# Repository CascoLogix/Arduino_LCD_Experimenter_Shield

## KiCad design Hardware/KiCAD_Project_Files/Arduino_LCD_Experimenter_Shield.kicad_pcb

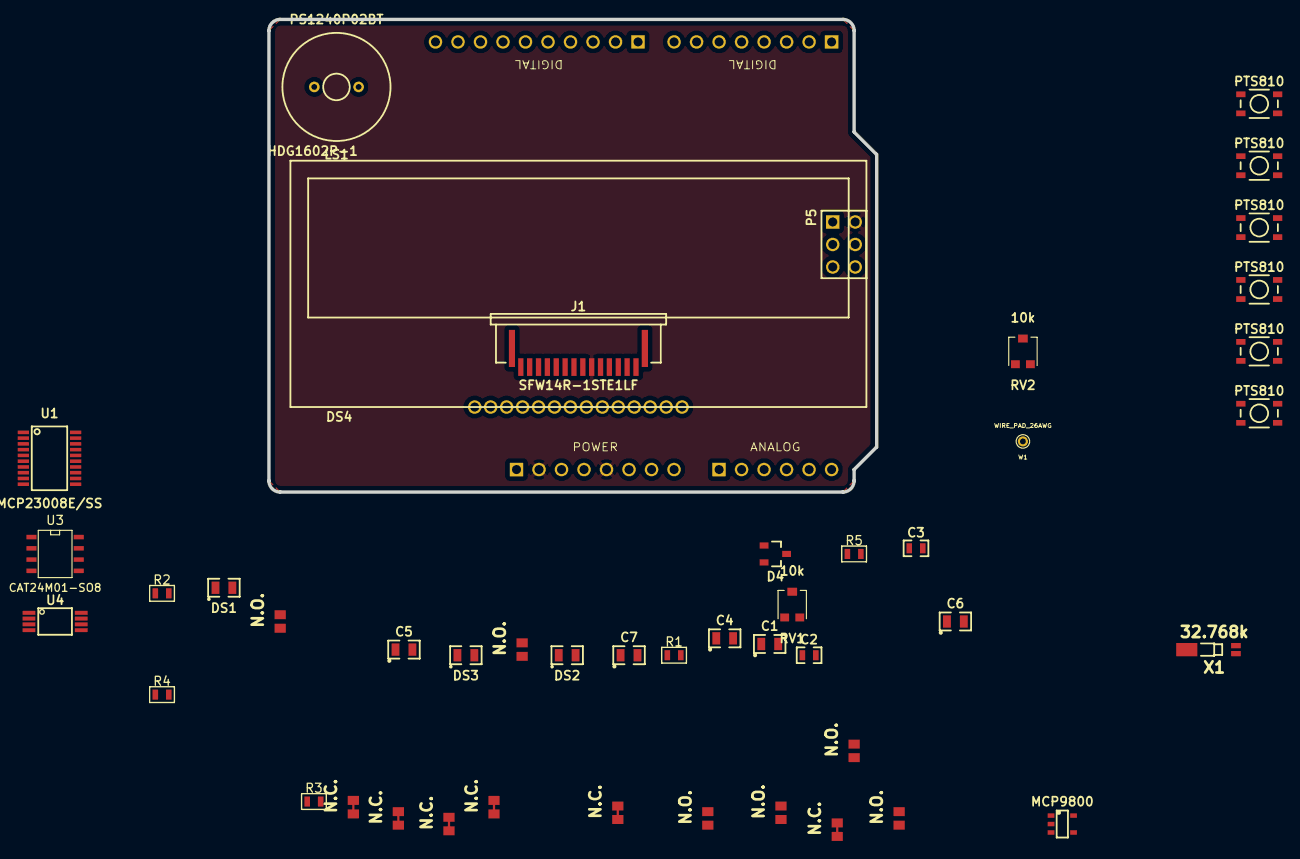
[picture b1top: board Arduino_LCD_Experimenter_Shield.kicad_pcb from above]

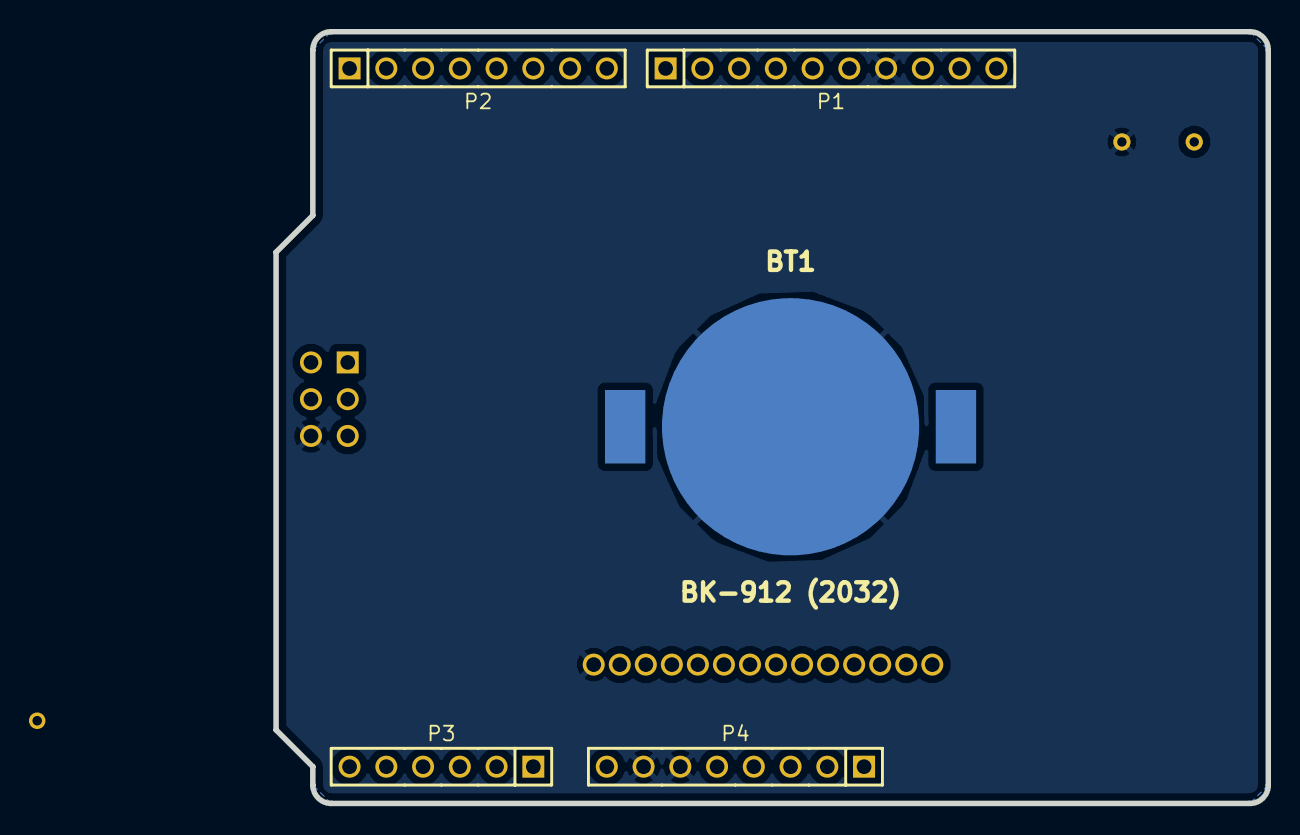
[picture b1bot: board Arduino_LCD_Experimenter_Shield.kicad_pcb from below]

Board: 2 copper layers, 68.6 x 53.3 mm, 51 parts (5 on the bottom side), 46 nets, no tracks yet.

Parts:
BT1: BK-912 (2032); CR2032_MPD_BK912_SMT
C1, C4, C5, C6, C7: 10uF; CP0805
C2, C3: 8pF; C0603
D4: BAV70L; SOT-23-3
DS1, DS2, DS3: YEL; DS0805
DS4: HDG1602P-1
J1: SFW14R-1STE1LF; FFC_14P_1.0MM_SMT
LK1, LK2, LK3, LK7, LK9, LK10: N.O.; SOLDER_LINK_NO
LK4, LK5, LK6, LK8, LK11, LK12: N.C.; SOLDER_LINK_NC
LS1: PS1240P02BT; PS1240P02BT_PTH
P1: 1X10 HEADER; HEADER_M_2.54MM_1R10P_ST_AU_PTH
P2, P4: 1X8 HEADER; HEADER_M_2.54MM_1R8P_ST_AU_PTH
P3: 1X6 HEADER; HEADER_M_2.54MM_1R6P_ST_AU_PTH
P5: 2X3 HEADER; HEADER_100MIL_2R6P_PTH
R1, R2, R3: 270; R0603
R4, R5: 4.7k; R0603
RV1, RV2: 10k; POT_TRIM_PVZ3_SMT
SW1, SW2, SW3, SW4, SW5, SW6: PTS810; PTS810_SMT
U1: MCP23008E/SS; TSSOP-20
U2: MCP9800; SOT-23-5
U3: CAT24M01-SO8; SO-8
U4: MCP7940M-I/ST; TSSOP-8
W1: WIRE_PAD_26AWG
X1: 32.768k; AB26TRQ

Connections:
+5V: C1.1, C4.1, C5.1, C6.1, D4.2, DS4.9, J1.9, LK1.1, LK2.1, LK3.1, LK9.1, LK10.1, P4.2, P4.5, P5.2, R1.1, R2.1, R3.1, R4.1, R5.1, RV1.3, U1.20, U2.1, U3.8
AD2: P3.3, RV2.3
AD3: LK7.1, P3.4
AD4/SDA: P1.9, P3.5, R4.2, U1.2, U2.5, U3.5, U4.5
AD5/SCL: P1.10, P3.6, R5.2, U1.1, U2.4, U3.6, U4.6
D0: DS4.8, J1.8
D1: DS4.7, J1.7
D2: DS4.6, J1.6
D3: DS4.5, J1.5
D4: DS4.4, J1.4, P2.5
D5: DS4.3, J1.3, P2.6
D6: DS4.2, J1.2, P2.7
D7: DS4.1, J1.1, P2.8
E: DS4.10, J1.10, P1.1
GND: BT1.2, C1.2, C2.1, C3.1, C4.2, C5.2, C6.2, C7.2, DS4.14, J1.14, LK4.2, LK5.2, LK6.2, LK8.2, LK11.2, LK12.2, LS1.2, P1.7, P4.6, P4.7, P5.6, RV1.1, RV2.1, SW1.1, SW1.2, SW2.3, SW2.4, SW3.3, SW3.4, SW4.3, SW4.4, SW5.3, SW5.4, SW6.3, SW6.4, U1.9, U2.2, U3.4, U3.7, U4.4, X1.3
IO2/INT0: P2.3, U4.7
IO3/INT1: P2.4, U1.8
IO9: DS4.12, J1.12, P1.2
IO11/MOSI: P1.4, P5.4
IO12/MISO: P1.5, P5.1
IO13/SCK: P1.6, P5.3
unnamed: LK3.2, LK6.1, U1.3
unnamed: LK2.2, LK5.1, U1.4
unnamed: LK1.2, LK4.1, U1.5
unnamed: LS1.1, RV2.2
unnamed: C2.2, U4.2, X1.1
unnamed: DS1.K, U1.17
unnamed: C3.2, U4.1, X1.2
unnamed: DS2.K, U1.18
unnamed: BT1.1, BT1.3, D4.1
unnamed: C7.1, D4.3, U4.8
unnamed: LK10.2, LK12.1, U3.3
unnamed: LK9.2, LK11.1, U3.2
unnamed: U2.3, W1.1
unnamed: SW3.1, SW3.2, U1.13
unnamed: SW2.1, SW2.2, U1.12
unnamed: SW4.1, SW4.2, U1.14
unnamed: SW5.1, SW5.2, U1.15
unnamed: SW6.1, SW6.2, U1.16
unnamed: DS3.K, U1.19
unnamed: DS1.A, R1.2
unnamed: DS2.A, R2.2
unnamed: DS3.A, R3.2
RESET: P4.3, P5.5, SW1.3, SW1.4, U1.6
RW: DS4.11, J1.11, LK7.2, LK8.1
V0: DS4.13, J1.13, RV1.2

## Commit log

2014-12-10 Created new decals and footprints with 3D models
2014-12-10 Saved files after previous commit, otherwise no change.
2014-12-10 Updated layout to include transducer and pushbutton footprints with 3D models.
